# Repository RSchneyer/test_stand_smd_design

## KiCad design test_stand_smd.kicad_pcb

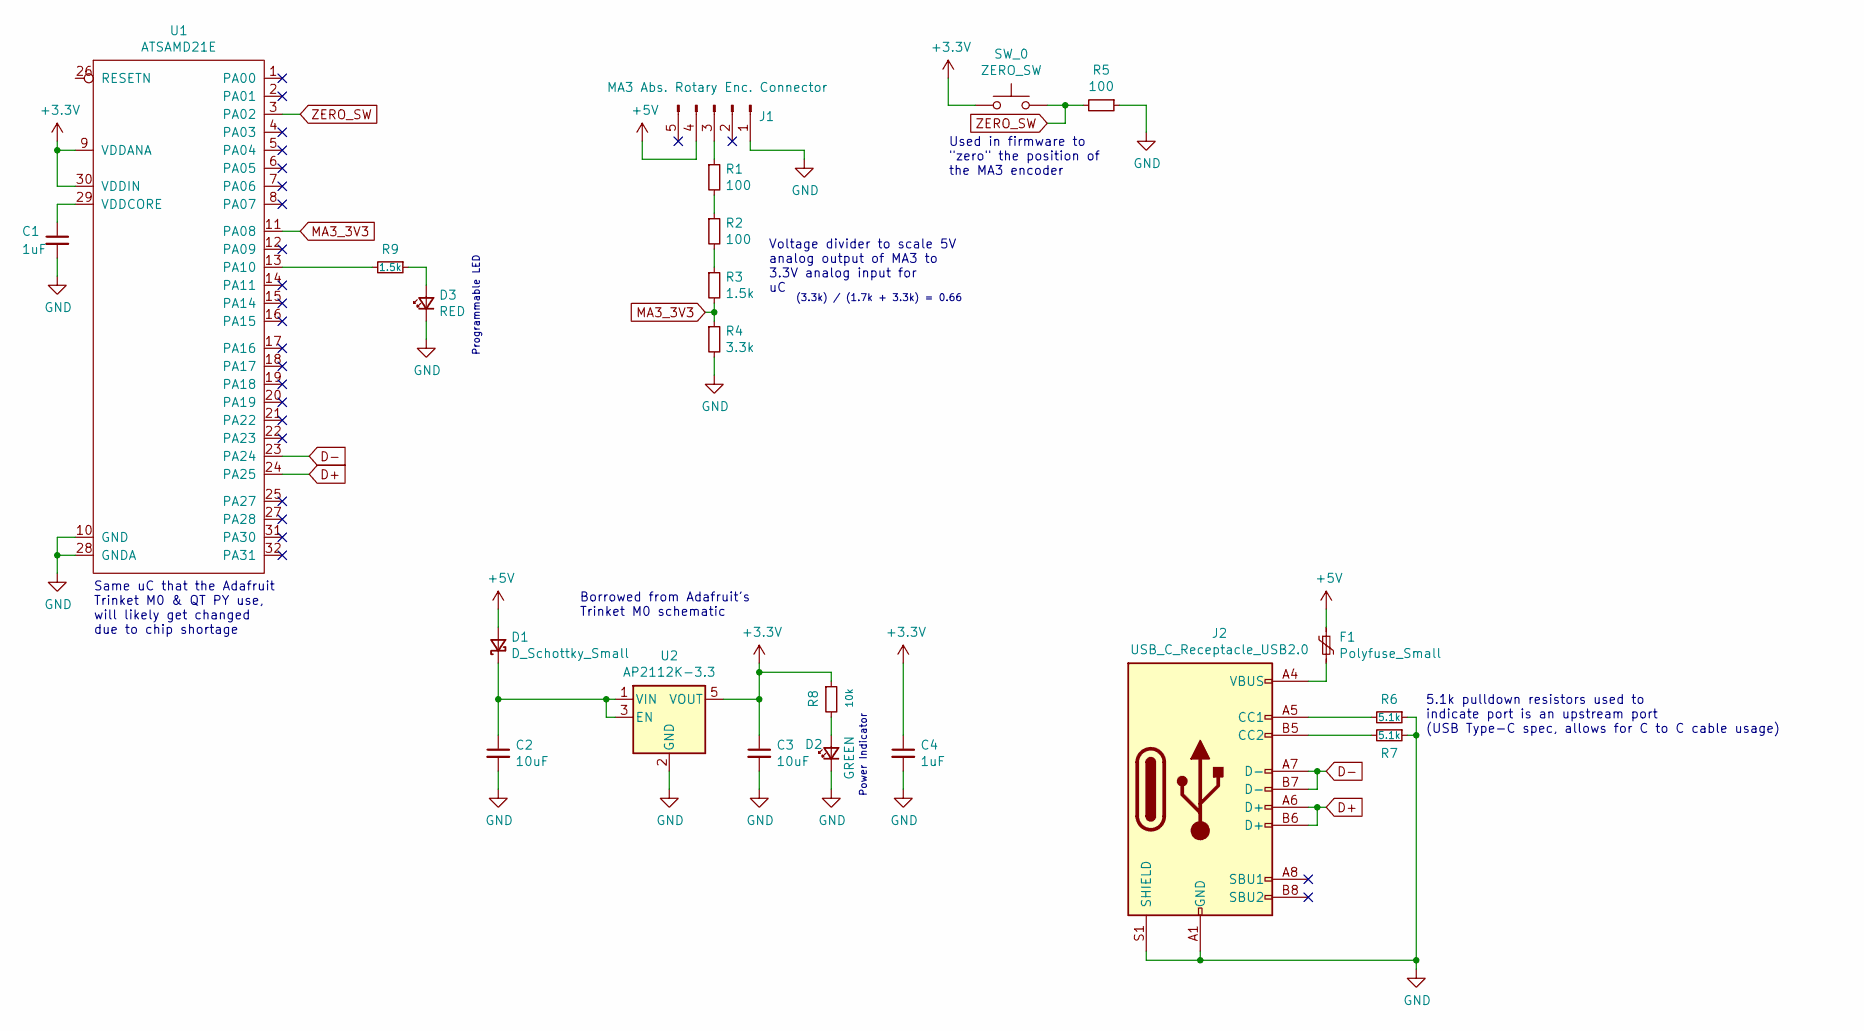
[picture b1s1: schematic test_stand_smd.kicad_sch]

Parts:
C1: 1uF; C_0603_1608Metric; LCSC C15849
C2, C3: 10uF; C_0603_1608Metric
C4: 1uF; C_0603_1608Metric
D1: D_Schottky_Small; D_0603_1608Metric
D2: GREEN; LED_0603_1608Metric; LCSC C2290
D3: RED; LED_0603_1608Metric; LCSC C2286
F1: Polyfuse_Small; Fuse_0603_1608Metric
J1: MA3 Abs. Rotary Enc. Connector; PinHeader_1x05_P2.54mm_Horizontal
J2: USB_C_Receptacle_USB2.0; USB_C_Receptacle_HRO_TYPE-C-31-M-12
R1, R2, R5: 100; R_0603_1608Metric; LCSC C22775
R3, R9: 1.5k; R_0603_1608Metric; LCSC C83059
R4: 3.3k; R_0603_1608Metric; LCSC C22978
R6, R7: 5.1k; R_0603_1608Metric
R8: 10k; R_0603_1608Metric
SW_0: ZERO_SW; SW_Push_SPST_NO_Alps_SKRK
U1: ATSAMD21E; QFN-32-1EP_4x4mm_P0.4mm_EP2.9x2.9mm; LCSC C220692
U2: AP2112K-3.3; SOT-23-5; LCSC C51118

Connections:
+3V3: C3.1, C4.1, R8.1, SW_0.1, U1.9 (VDDANA), U1.30 (VDDIN), U2.5 (VOUT); also elsewhere on the board
+5V: D1.2 (A), F1.1, J1.4
D+: J2.A6 (D+), J2.B6 (D+), U1.24 (PA25)
D-: J2.A7 (D-), J2.B7 (D-), U1.23 (PA24)
GND: C1.2, C2.2, C3.2, C4.2, D2.1 (K), D3.1 (K), J1.1, J2.A1 (GND), J2.A12 (GND), J2.B1 (GND), J2.B12 (GND), J2.S1 (SHIELD), R4.2, R5.1, R6.1, R7.1, U1.10 (GND), U1.28 (GNDA), U2.2 (GND)
HOME_SW: R5.2, SW_0.2, U1.3 (PA02); also elsewhere on the board
MA3_3V3: R3.2, R4.1, U1.11 (PA08)
unnamed: C1.1, U1.29 (VDDCORE)
unnamed: C2.1, D1.1 (K), U2.1 (VIN), U2.3 (EN)
unnamed: D2.2 (A), R8.2
unnamed: D3.2 (A), R9.1
unnamed: F1.2, J2.A4 (VBUS), J2.A9 (VBUS), J2.B4 (VBUS), J2.B9 (VBUS)
unnamed: J1.3, R1.1
unnamed: J2.A5 (CC1), R6.2
unnamed: J2.B5 (CC2), R7.2
unnamed: R1.2, R2.1
unnamed: R2.2, R3.1
unnamed: R9.2, U1.13 (PA10)
unnamed 40: U1.26 (RESETN); also elsewhere on the board

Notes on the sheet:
Programmable LED
Used in firmware to "zero" the position of the MA3 encoder
Power Indicator
Same uC that the Adafruit Trinket M0 & QT PY use, will likely get changed due to chip shortage
(3.3k) / (1.7k + 3.3k) = 0.66
Borrowed from Adafruit's Trinket M0 schematic
5.1k pulldown resistors used to indicate port is an upstream port (USB Type-C spec, allows for C to C cable usage)
Voltage divider to scale 5V analog output of MA3 to 3.3V analog input for uC

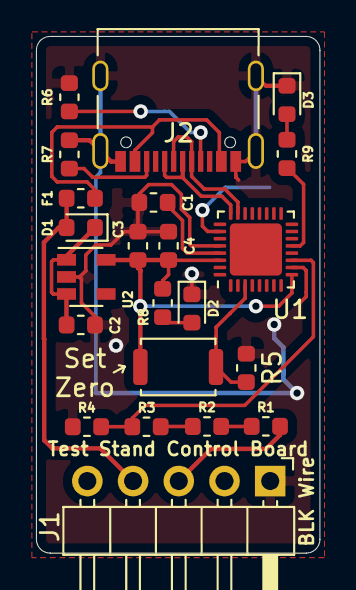
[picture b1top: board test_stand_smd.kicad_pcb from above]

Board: 2 copper layers, 15.7 x 28.7 mm, 23 parts (1 on the bottom side), 19 nets.

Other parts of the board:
RESET: TestPoint_Pad_D1.0mm
SW_HOME1: SW_Push; SW_Push_SPST_NO_Alps_SKRK

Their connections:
+3V3: SW_HOME1.1; also elsewhere on the board
HOME_SW: SW_HOME1.2; also elsewhere on the board
unnamed 40: RESET.1; also elsewhere on the board

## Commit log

2022-01-26 Added schematic comments
2022-01-29 upgraded to kicad 6
